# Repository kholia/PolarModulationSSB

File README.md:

Experiments with SSB signal generation using `Polar Modulation`.

This documentation is pretty rough at the moment - please excuse!

This was inspired by https://dl0tz.de/polar/index_en.html work. The AD9850 adaptation is inspired by G4GX0 (Ron)'s work - thank you.

Hardware: RP2350-Zero MCU board + Fast Si5351 module with TCXO (included)!

Software: Run `make` from the `firmware_ssb` folder.

Demo:

Updates:

15-Feb-2026: The generated SSB signal's audio quality and fidelity is not good at all. This being said, one can still make out the original message if one squints hard enough. We only do phase modulation currently and are still building out the amplitude ("envelope") restoration hardware (the code for this is ready on Pin 0).

18-Feb-2026: The generated SSB signal's audio quality and fidelity is pretty ok'ish now! We are yet to hookup the envelope restoration ("AM") circuitry.

References:

- https://rfcorner.in/posts/the-polar-express/

- https://github.com/kholia/Colorlight-5A-75B

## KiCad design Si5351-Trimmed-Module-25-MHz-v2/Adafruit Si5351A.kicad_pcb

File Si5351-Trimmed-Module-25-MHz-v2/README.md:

Changes in `Si5351-Trimmed-Module-25-MHz-v2` version:

- I2C pull-ups are now 1KΩ to enable Polar Modulation experiments!

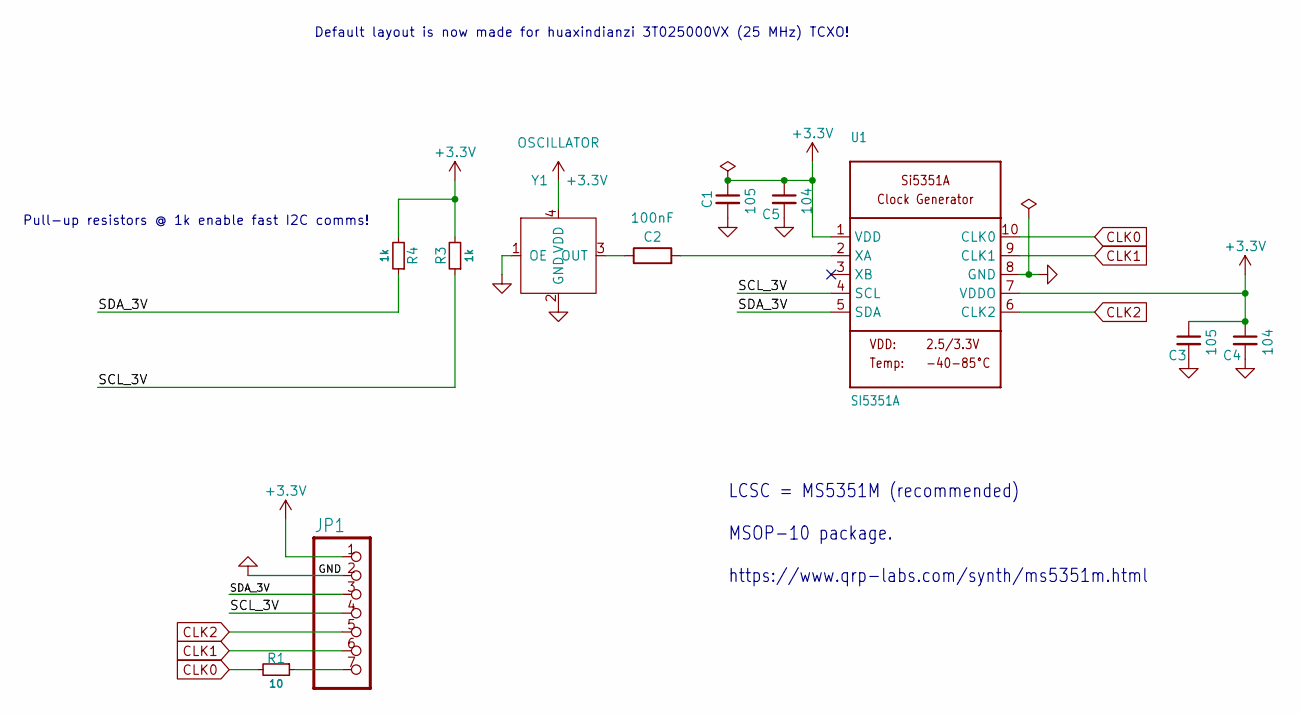
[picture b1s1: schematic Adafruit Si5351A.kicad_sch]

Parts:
C1, C3: 105; C_0603_1608Metric
C2: 100nF; C_0603_1608Metric
C4, C5: 104; C_0603_1608Metric
JP1: 1X07_ROUND_76
R1: 10; R_0805_2012Metric_Pad1.20x1.40mm_HandSolder
R3, R4: 1k; R_0805_2012Metric_Pad1.20x1.40mm_HandSolder
U1: SI5351A; MSOP-10_3x3mm_P0.5mm
Y1: OSCILLATOR; OSC-SMD_4P-L3.2-W2.5-BL-1

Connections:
+3.3V: C1.1, C3.1, C4.1, C5.1, JP1.1, R3.2, R4.2, U1.1 (VDD), U1.7 (VDDO), Y1.4 (VDD)
/SCL_3V: JP1.4, R3.1, U1.4 (SCL)
/SDA_3V: JP1.3, R4.1, U1.5 (SDA)
CLK0: R1.2, U1.10 (CLK0)
CLK1: JP1.6, U1.9 (CLK1)
CLK2: JP1.5, U1.6 (CLK2)
GND: C1.2, C3.2, C4.2, C5.2, JP1.2, U1.8 (GND), Y1.1 (OE), Y1.2 (GND)
unnamed: JP1.7, R1.1
unnamed: C2.2, U1.2 (XA)
unnamed: C2.1, Y1.3 (OUT)

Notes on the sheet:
Default layout is now made for huaxindianzi 3T025000VX (25 MHz) TCXO!
Pull-up resistors @ 1k enable fast I2C comms!
LCSC = MS5351M (recommended) MSOP-10 package. https://www.qrp-labs.com/synth/ms5351m.html

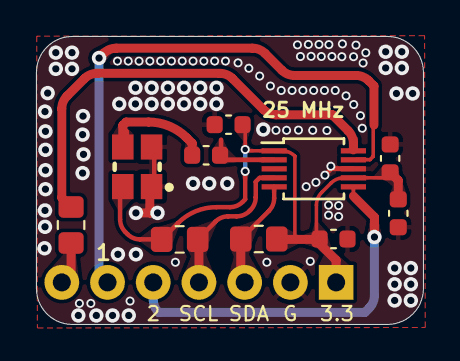
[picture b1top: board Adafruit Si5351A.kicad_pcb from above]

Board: 2 copper layers, 21.5 x 16.0 mm, 11 parts (0 on the bottom side), 10 nets.

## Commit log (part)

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2026-02-21 SSB with Polar Modulation PoC
